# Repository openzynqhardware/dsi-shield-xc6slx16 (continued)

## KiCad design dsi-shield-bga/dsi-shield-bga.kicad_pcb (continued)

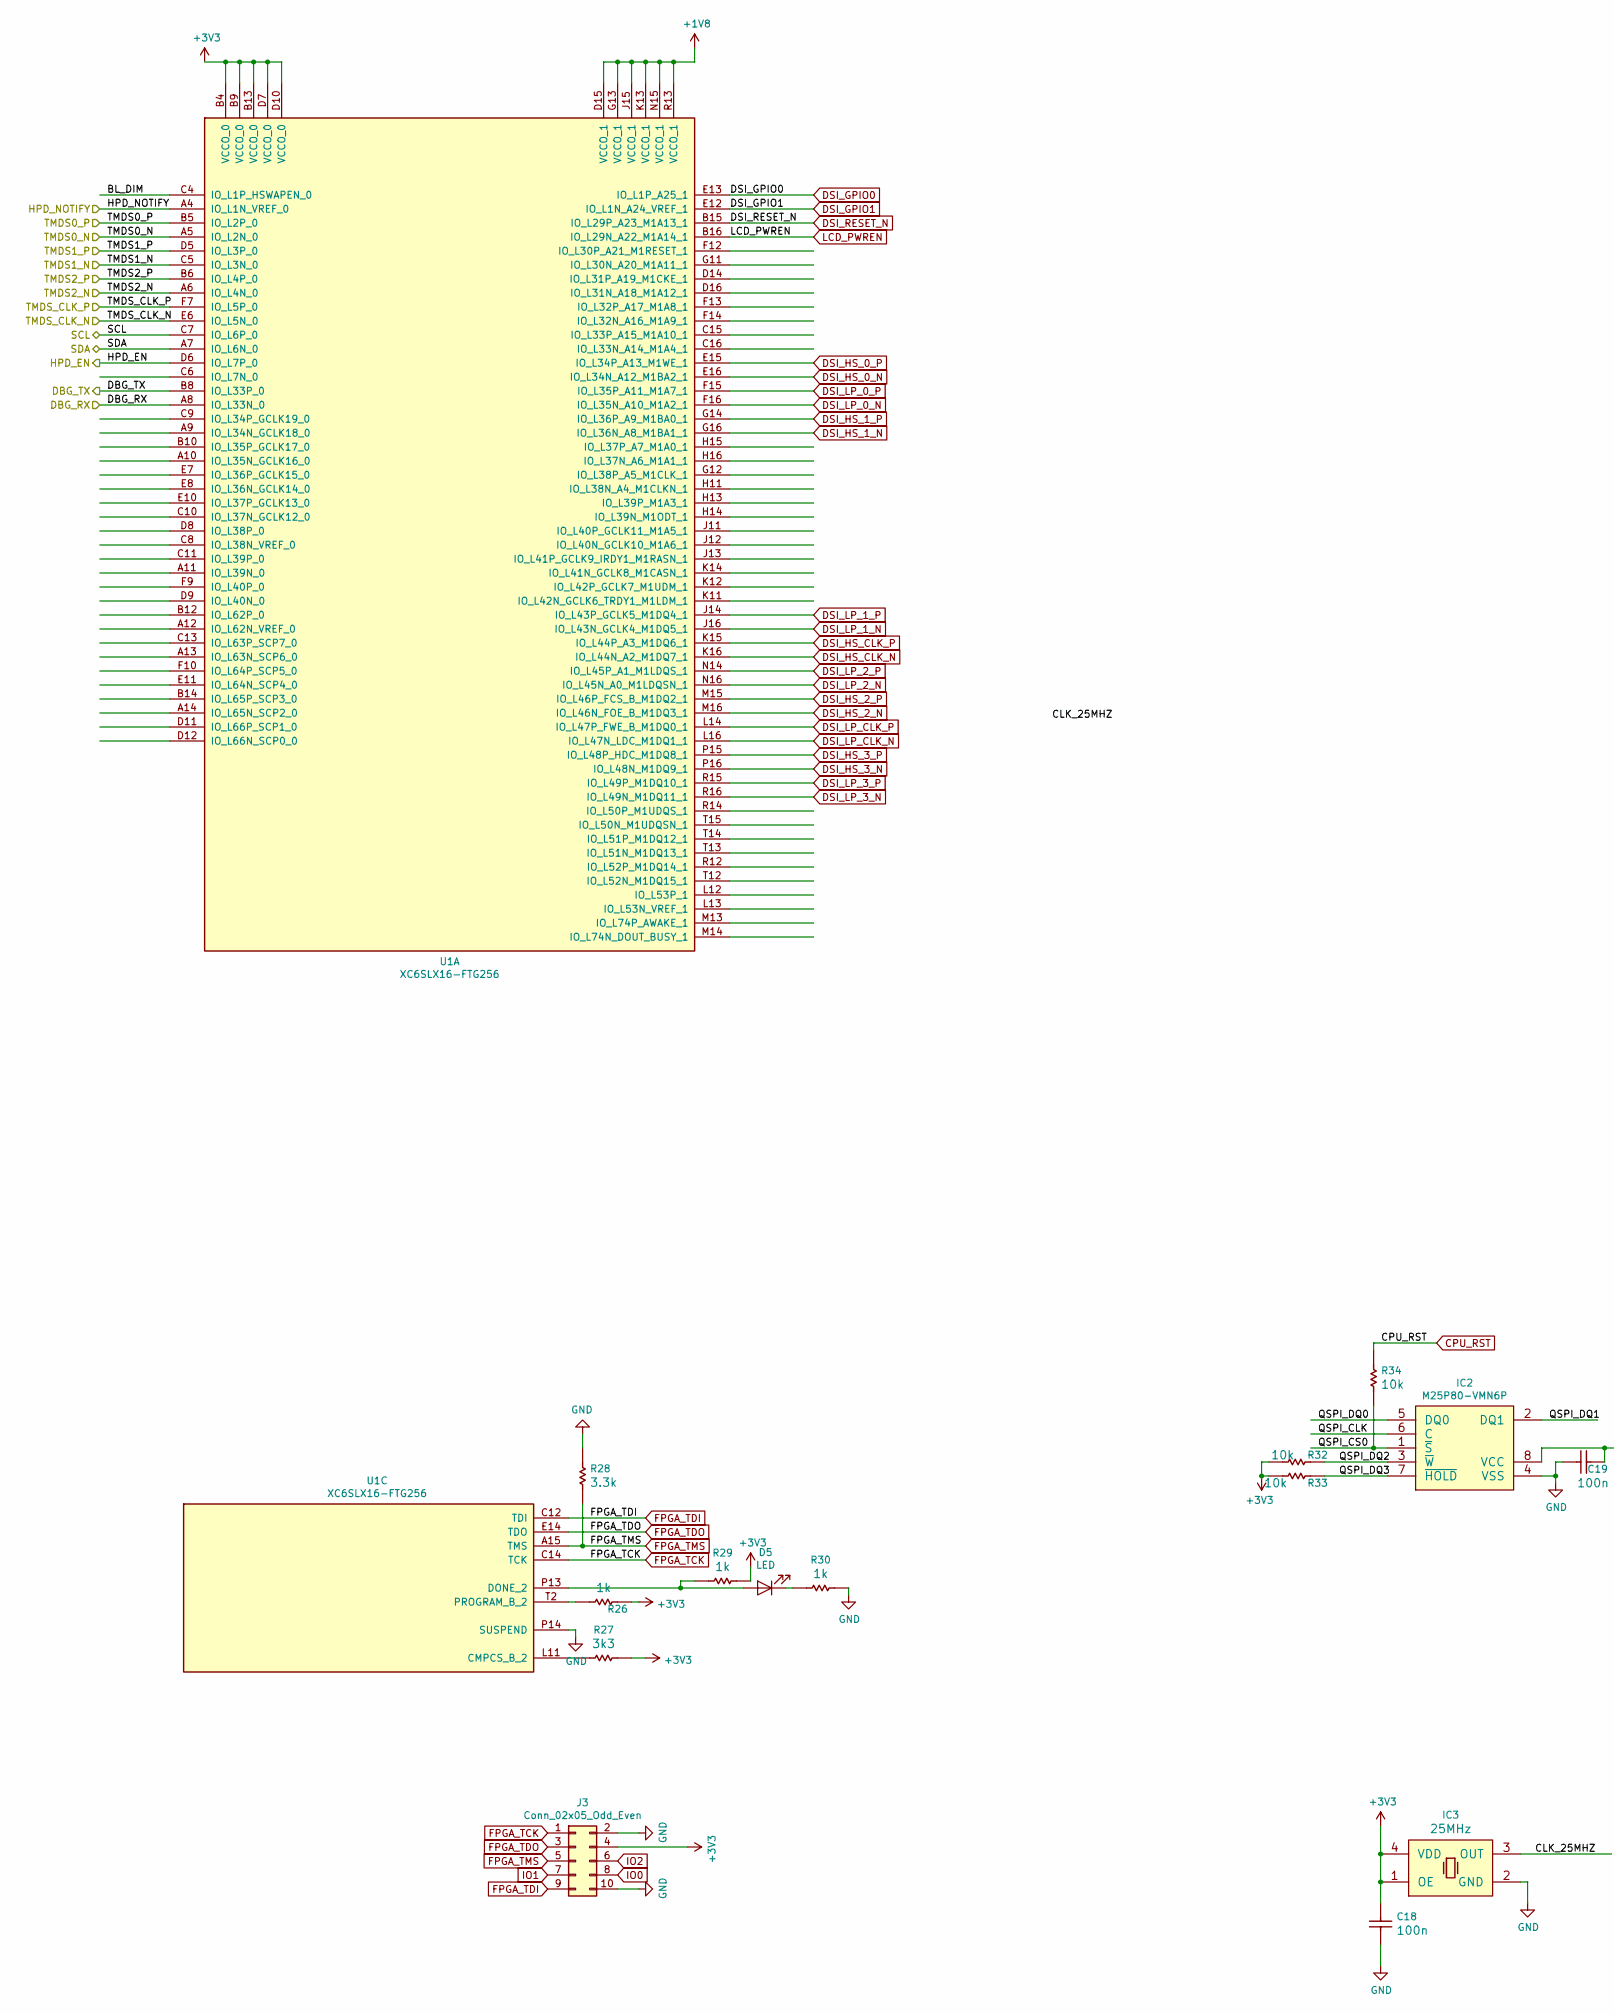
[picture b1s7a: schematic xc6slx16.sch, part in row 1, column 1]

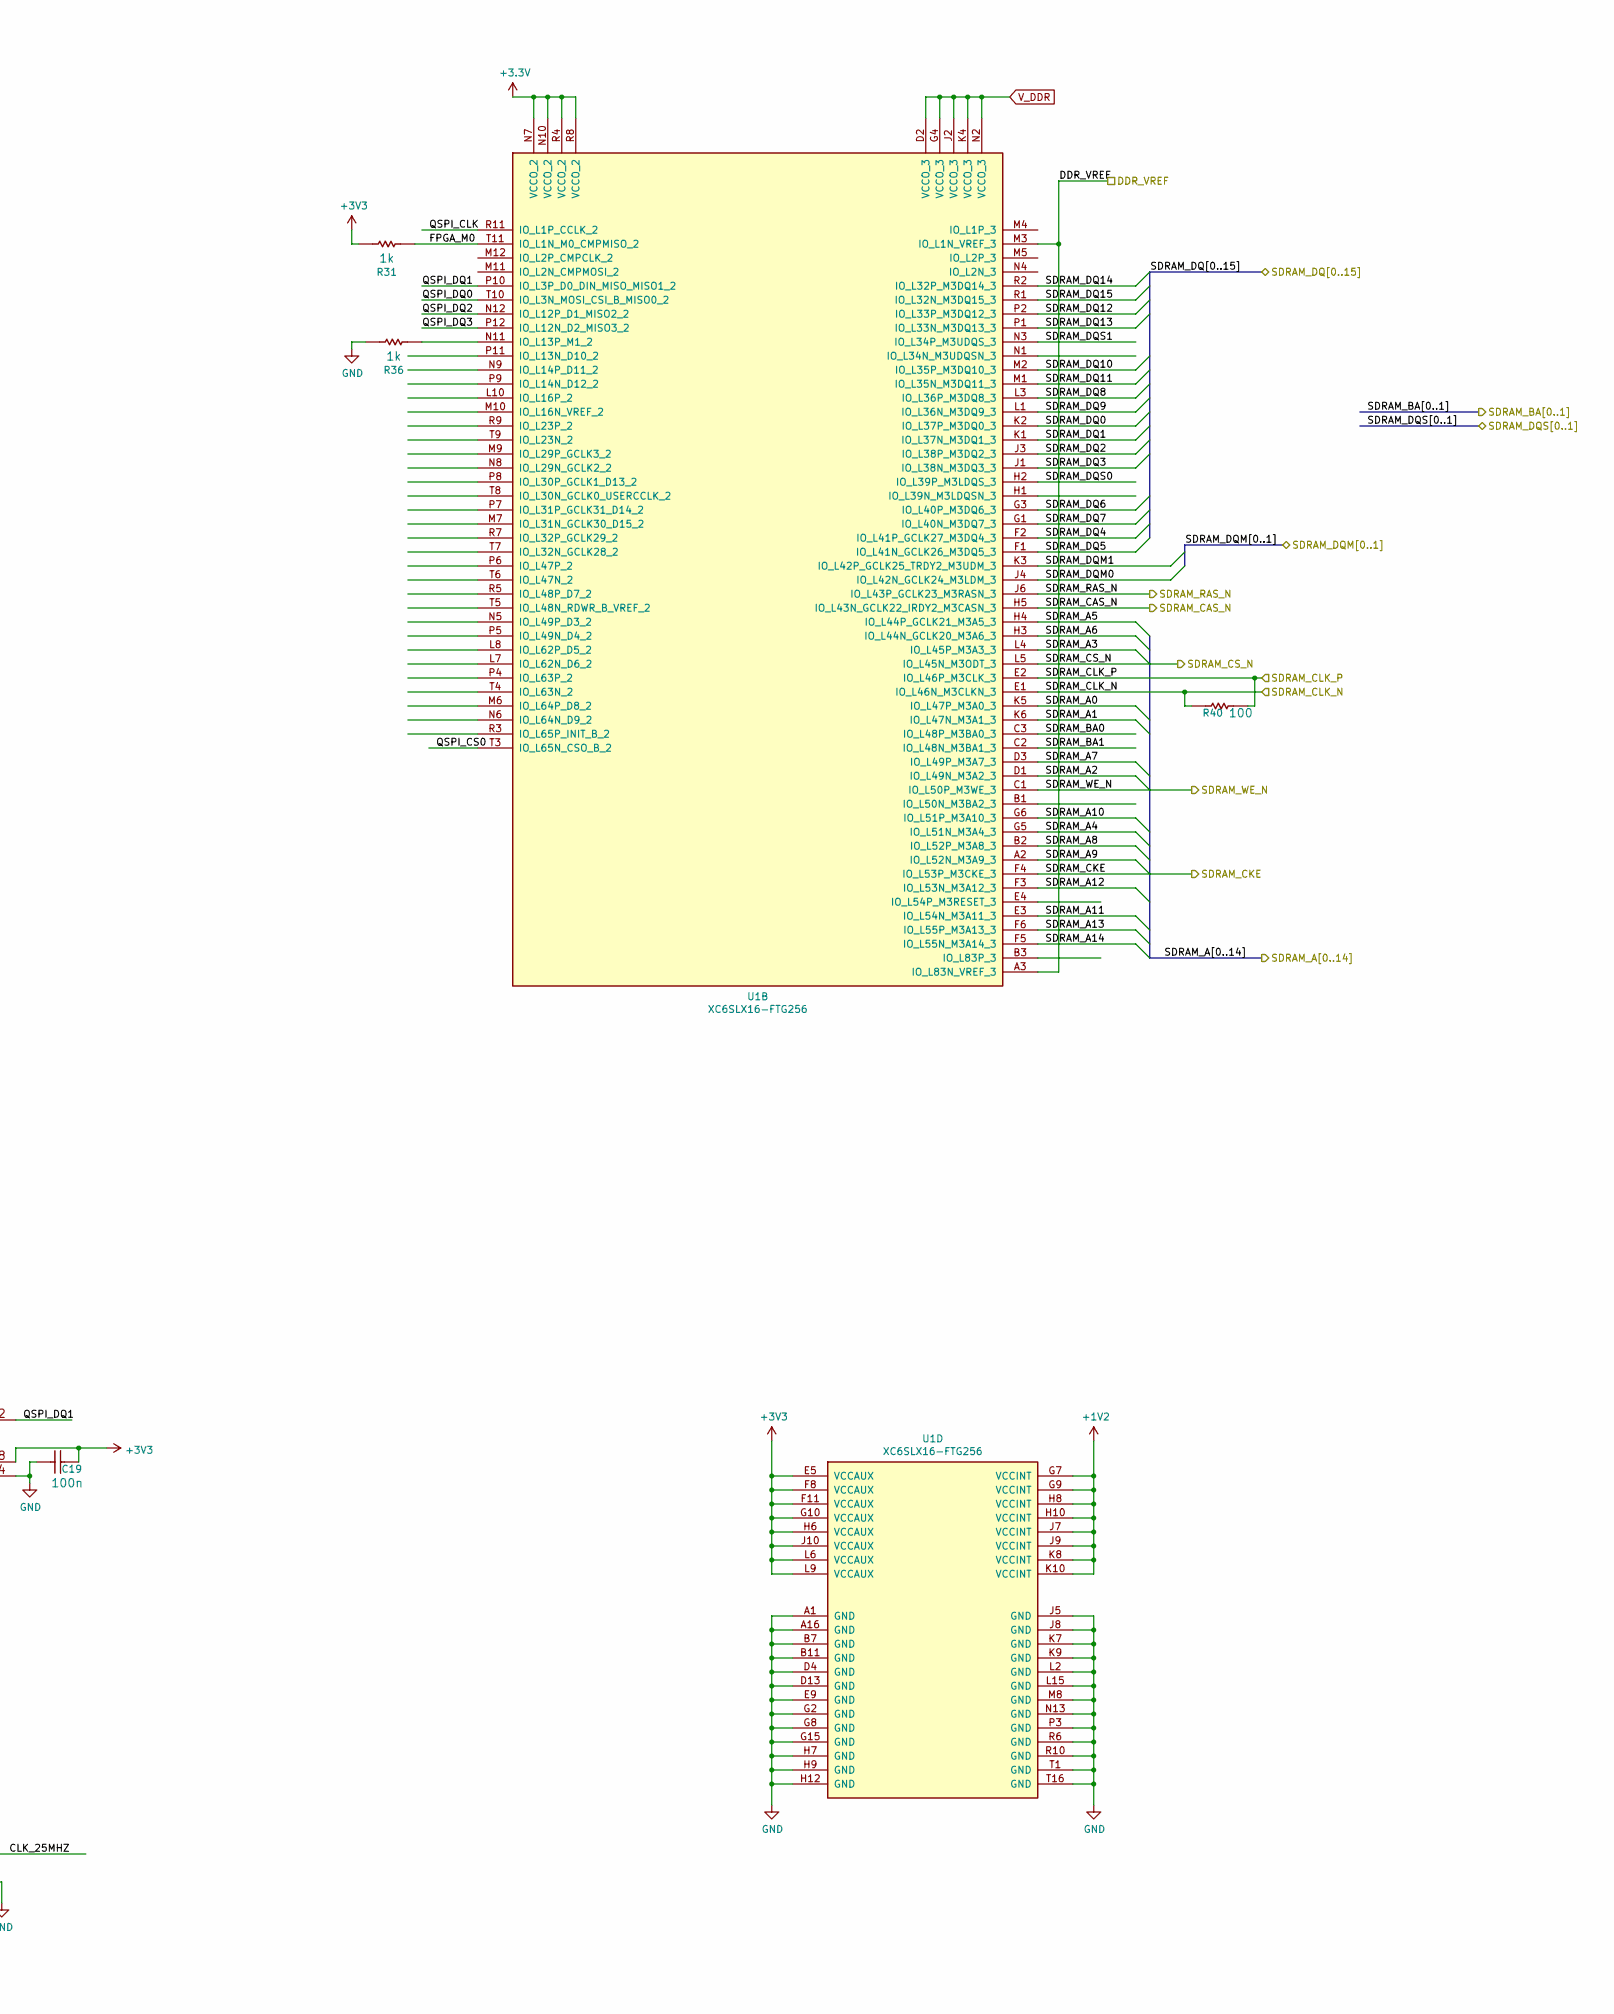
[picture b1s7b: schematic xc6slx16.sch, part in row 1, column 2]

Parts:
C18, C19: 100n; C_0402_1005Metric
D5: LED; LED_0603_1608Metric
IC2: M25P80-VMN6P; DFN-8-1EP_6x5mm_P1.27mm_EP4x4mm
IC3: 25MHz; Oscillator_SMD_Abracon_ASE-4Pin_3.2x2.5mm_HandSoldering
J3: Conn_02x05_Odd_Even; debugger_2x05_P1.27mm_Vertical
R26, R29, R30, R31, R36: 1k; R_0402_1005Metric
R27: 3k3; R_0402_1005Metric
R28: 3.3k; R_0402_1005Metric
R32, R33, R34: 10k; R_0402_1005Metric
R40: 100; R_0402_1005Metric
U1: XC6SLX16-FTG256; Xilinx_FTG256

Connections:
+1V2: U1.G7 (VCCINT), U1.G9 (VCCINT), U1.H8 (VCCINT), U1.H10 (VCCINT), U1.J7 (VCCINT), U1.J9 (VCCINT), U1.K8 (VCCINT), U1.K10 (VCCINT); also elsewhere on the board
+1V8: U1.D15 (VCCO_1), U1.G13 (VCCO_1), U1.J15 (VCCO_1), U1.K13 (VCCO_1), U1.N15 (VCCO_1), U1.R13 (VCCO_1); also elsewhere on the board
/Sheet5F12EB4F/DBG_RX: U1.B8 (IO_L33P_0); also elsewhere on the board
/Sheet5F173767/BL_DIM: U1.C4 (IO_L1P_HSWAPEN_0)
/Sheet5F173767/CLK_25MHZ: IC3.3 (OUT)
/Sheet5F173767/DBG_RX: U1.A8 (IO_L33N_0); also elsewhere on the board
/Sheet5F173767/DDR_VREF: U1.A3 (IO_L83N_VREF_3), U1.M3 (IO_L1N_VREF_3); also elsewhere on the board
/Sheet5F173767/FPGA_M0: R31.1, U1.T11 (IO_L1N_M0_CMPMISO_2)
/Sheet5F173767/HPD_EN: U1.D6 (IO_L7P_0); also elsewhere on the board
/Sheet5F173767/HPD_NOTIFY: U1.A4 (IO_L1N_VREF_0); also elsewhere on the board
/Sheet5F173767/QSPI_CLK: IC2.6 (C), U1.R11 (IO_L1P_CCLK_2)
/Sheet5F173767/QSPI_CS0: IC2.1 (~S), R34.2, U1.T3 (IO_L65N_CSO_B_2)
/Sheet5F173767/QSPI_DQ0: IC2.5 (DQ0), U1.T10 (IO_L3N_MOSI_CSI_B_MISO0_2)
/Sheet5F173767/QSPI_DQ1: IC2.2 (DQ1), U1.P10 (IO_L3P_D0_DIN_MISO_MISO1_2)
/Sheet5F173767/QSPI_DQ2: IC2.3 (~W), R32.2, U1.N12 (IO_L12P_D1_MISO2_2)
/Sheet5F173767/QSPI_DQ3: IC2.7 (~HOLD), R33.2, U1.P12 (IO_L12N_D2_MISO3_2)
/Sheet5F173767/SCL: U1.C7 (IO_L6P_0); also elsewhere on the board
/Sheet5F173767/SDA: U1.A7 (IO_L6N_0); also elsewhere on the board
/Sheet5F173767/SDRAM_A0: U1.K5 (IO_L47P_M3A0_3); also elsewhere on the board
/Sheet5F173767/SDRAM_A1: U1.K6 (IO_L47N_M3A1_3); also elsewhere on the board
/Sheet5F173767/SDRAM_A2: U1.D1 (IO_L49N_M3A2_3); also elsewhere on the board
/Sheet5F173767/SDRAM_A3: U1.L4 (IO_L45P_M3A3_3); also elsewhere on the board
/Sheet5F173767/SDRAM_A4: U1.G5 (IO_L51N_M3A4_3); also elsewhere on the board
/Sheet5F173767/SDRAM_A5: U1.H4 (IO_L44P_GCLK21_M3A5_3); also elsewhere on the board
/Sheet5F173767/SDRAM_A6: U1.H3 (IO_L44N_GCLK20_M3A6_3); also elsewhere on the board
/Sheet5F173767/SDRAM_A7: U1.D3 (IO_L49P_M3A7_3); also elsewhere on the board
/Sheet5F173767/SDRAM_A8: U1.B2 (IO_L52P_M3A8_3); also elsewhere on the board
/Sheet5F173767/SDRAM_A9: U1.A2 (IO_L52N_M3A9_3); also elsewhere on the board
/Sheet5F173767/SDRAM_A10: U1.G6 (IO_L51P_M3A10_3); also elsewhere on the board
/Sheet5F173767/SDRAM_A11: U1.E3 (IO_L54N_M3A11_3); also elsewhere on the board
/Sheet5F173767/SDRAM_A12: U1.F3 (IO_L53N_M3A12_3); also elsewhere on the board
/Sheet5F173767/SDRAM_A13: U1.F6 (IO_L55P_M3A13_3); also elsewhere on the board
/Sheet5F173767/SDRAM_A14: U1.F5 (IO_L55N_M3A14_3)
/Sheet5F173767/SDRAM_BA0: U1.C3 (IO_L48P_M3BA0_3); also elsewhere on the board
/Sheet5F173767/SDRAM_BA1: U1.C2 (IO_L48N_M3BA1_3); also elsewhere on the board
/Sheet5F173767/SDRAM_CAS_N: U1.H5 (IO_L43N_GCLK22_IRDY2_M3CASN_3); also elsewhere on the board
/Sheet5F173767/SDRAM_CKE: U1.F4 (IO_L53P_M3CKE_3); also elsewhere on the board
/Sheet5F173767/SDRAM_CLK_N: R40.1, U1.E1 (IO_L46N_M3CLKN_3); also elsewhere on the board
/Sheet5F173767/SDRAM_CLK_P: R40.2, U1.E2 (IO_L46P_M3CLK_3); also elsewhere on the board
/Sheet5F173767/SDRAM_CS_N: U1.L5 (IO_L45N_M3ODT_3); also elsewhere on the board
/Sheet5F173767/SDRAM_DQ0: U1.K2 (IO_L37P_M3DQ0_3); also elsewhere on the board
/Sheet5F173767/SDRAM_DQ1: U1.K1 (IO_L37N_M3DQ1_3); also elsewhere on the board
/Sheet5F173767/SDRAM_DQ2: U1.J3 (IO_L38P_M3DQ2_3); also elsewhere on the board
/Sheet5F173767/SDRAM_DQ3: U1.J1 (IO_L38N_M3DQ3_3); also elsewhere on the board
/Sheet5F173767/SDRAM_DQ4: U1.F2 (IO_L41P_GCLK27_M3DQ4_3); also elsewhere on the board
/Sheet5F173767/SDRAM_DQ5: U1.F1 (IO_L41N_GCLK26_M3DQ5_3); also elsewhere on the board
/Sheet5F173767/SDRAM_DQ6: U1.G3 (IO_L40P_M3DQ6_3); also elsewhere on the board
/Sheet5F173767/SDRAM_DQ7: U1.G1 (IO_L40N_M3DQ7_3); also elsewhere on the board
/Sheet5F173767/SDRAM_DQ8: U1.L3 (IO_L36P_M3DQ8_3); also elsewhere on the board
/Sheet5F173767/SDRAM_DQ9: U1.L1 (IO_L36N_M3DQ9_3); also elsewhere on the board
/Sheet5F173767/SDRAM_DQ10: U1.M2 (IO_L35P_M3DQ10_3); also elsewhere on the board
/Sheet5F173767/SDRAM_DQ11: U1.M1 (IO_L35N_M3DQ11_3); also elsewhere on the board
/Sheet5F173767/SDRAM_DQ12: U1.P2 (IO_L33P_M3DQ12_3); also elsewhere on the board
/Sheet5F173767/SDRAM_DQ13: U1.P1 (IO_L33N_M3DQ13_3); also elsewhere on the board
/Sheet5F173767/SDRAM_DQ14: U1.R2 (IO_L32P_M3DQ14_3); also elsewhere on the board
/Sheet5F173767/SDRAM_DQ15: U1.R1 (IO_L32N_M3DQ15_3); also elsewhere on the board
/Sheet5F173767/SDRAM_DQM0: U1.J4 (IO_L42N_GCLK24_M3LDM_3); also elsewhere on the board
/Sheet5F173767/SDRAM_DQM1: U1.K3 (IO_L42P_GCLK25_TRDY2_M3UDM_3); also elsewhere on the board
/Sheet5F173767/SDRAM_DQS0: U1.H2 (IO_L39P_M3LDQS_3); also elsewhere on the board
/Sheet5F173767/SDRAM_DQS1: U1.N3 (IO_L34P_M3UDQS_3); also elsewhere on the board
/Sheet5F173767/SDRAM_RAS_N: U1.J6 (IO_L43P_GCLK23_M3RASN_3); also elsewhere on the board
/Sheet5F173767/SDRAM_WE_N: U1.C1 (IO_L50P_M3WE_3); also elsewhere on the board
/Sheet5F173767/TMDS0_N: U1.A5 (IO_L2N_0); also elsewhere on the board
/Sheet5F173767/TMDS0_P: U1.B5 (IO_L2P_0); also elsewhere on the board
/Sheet5F173767/TMDS1_N: U1.C5 (IO_L3N_0); also elsewhere on the board
/Sheet5F173767/TMDS1_P: U1.D5 (IO_L3P_0); also elsewhere on the board
/Sheet5F173767/TMDS2_N: U1.A6 (IO_L4N_0); also elsewhere on the board
/Sheet5F173767/TMDS2_P: U1.B6 (IO_L4P_0); also elsewhere on the board
/Sheet5F173767/TMDS_CLK_N: U1.E6 (IO_L5N_0); also elsewhere on the board
/Sheet5F173767/TMDS_CLK_P: U1.F7 (IO_L5P_0); also elsewhere on the board
CPU_RST: R34.1; also elsewhere on the board
DSI_GPIO0: U1.E13 (IO_L1P_A25_1); also elsewhere on the board
DSI_GPIO1: U1.E12 (IO_L1N_A24_VREF_1); also elsewhere on the board
DSI_HS_0_N: U1.E16 (IO_L34N_A12_M1BA2_1); also elsewhere on the board
DSI_HS_0_P: U1.E15 (IO_L34P_A13_M1WE_1); also elsewhere on the board
DSI_HS_1_N: U1.G16 (IO_L36N_A8_M1BA1_1); also elsewhere on the board
DSI_HS_1_P: U1.G14 (IO_L36P_A9_M1BA0_1); also elsewhere on the board
DSI_HS_2_N: U1.M16 (IO_L46N_FOE_B_M1DQ3_1); also elsewhere on the board
DSI_HS_2_P: U1.M15 (IO_L46P_FCS_B_M1DQ2_1); also elsewhere on the board
DSI_HS_3_N: U1.P16 (IO_L48N_M1DQ9_1); also elsewhere on the board
DSI_HS_3_P: U1.P15 (IO_L48P_HDC_M1DQ8_1); also elsewhere on the board
DSI_HS_CLK_N: U1.K16 (IO_L44N_A2_M1DQ7_1); also elsewhere on the board
DSI_HS_CLK_P: U1.K15 (IO_L44P_A3_M1DQ6_1); also elsewhere on the board
DSI_LP_0_N: U1.F16 (IO_L35N_A10_M1A2_1); also elsewhere on the board
DSI_LP_0_P: U1.F15 (IO_L35P_A11_M1A7_1); also elsewhere on the board
DSI_LP_1_N: U1.J16 (IO_L43N_GCLK4_M1DQ5_1); also elsewhere on the board
DSI_LP_1_P: U1.J14 (IO_L43P_GCLK5_M1DQ4_1); also elsewhere on the board
DSI_LP_2_N: U1.N16 (IO_L45N_A0_M1LDQSN_1); also elsewhere on the board
DSI_LP_2_P: U1.N14 (IO_L45P_A1_M1LDQS_1); also elsewhere on the board
DSI_LP_3_N: U1.R16 (IO_L49N_M1DQ11_1); also elsewhere on the board
DSI_LP_3_P: U1.R15 (IO_L49P_M1DQ10_1); also elsewhere on the board
DSI_LP_CLK_N: U1.L16 (IO_L47N_LDC_M1DQ1_1); also elsewhere on the board
DSI_LP_CLK_P: U1.L14 (IO_L47P_FWE_B_M1DQ0_1); also elsewhere on the board
DSI_RESET_N: U1.B15 (IO_L29P_A23_M1A13_1); also elsewhere on the board
FPGA_TCK: J3.1, U1.C14 (TCK); also elsewhere on the board
FPGA_TDI: J3.9, U1.C12 (TDI); also elsewhere on the board
FPGA_TDO: J3.3, U1.E14 (TDO); also elsewhere on the board
FPGA_TMS: J3.5, R28.2, U1.A15 (TMS); also elsewhere on the board
GND: C18.2, C19.1, IC2.4 (VSS), IC3.2 (GND), J3.2, J3.10, R28.1, R30.2, R36.2, U1.A1 (GND), U1.A16 (GND), U1.B7 (GND), U1.B11 (GND), U1.D4 (GND), U1.D13 (GND), U1.E9 (GND), U1.G2 (GND), U1.G8 (GND), U1.G15 (GND), U1.H7 (GND), U1.H9 (GND), U1.H12 (GND), U1.J5 (GND), U1.J8 (GND), U1.K7 (GND), U1.K9 (GND), U1.L2 (GND), U1.L15 (GND), U1.M8 (GND), U1.N13 (GND), U1.P3 (GND), U1.P14 (SUSPEND), U1.R6 (GND), U1.R10 (GND), U1.T1 (GND), U1.T16 (GND); also elsewhere on the board
IO0: J3.8
IO1: J3.7
IO2: J3.6
LCD_PWREN: U1.B16 (IO_L29N_A22_M1A14_1); also elsewhere on the board
unnamed: D5.1 (K), R30.1
unnamed: D5.2 (A), R29.1, U1.P13 (DONE_2)
unnamed: R26.1, U1.T2 (PROGRAM_B_2)
unnamed: R27.1, U1.L11 (CMPCS_B_2)
unnamed: R36.1, U1.N11 (IO_L13P_M1_2)
V_DDR: U1.D2 (VCCO_3), U1.G4 (VCCO_3), U1.J2 (VCCO_3), U1.K4 (VCCO_3), U1.N2 (VCCO_3); also elsewhere on the board

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
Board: 2 copper layers, 151 parts (11 on the bottom side), 141 nets, no tracks yet.

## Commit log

2020-07-18 init
2020-07-18 iphone4s lcd
2020-07-18 datasheet
2020-07-18 20200718
2020-07-18 20200719-1
2020-07-24 ddr sdram
2020-07-26 128MB DDR SDRAM
2020-08-08 20200808
2020-12-06 pin head
2020-12-07 8/18
